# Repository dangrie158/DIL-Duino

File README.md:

# DIL-Duino

<br /><span xmlns:dct="http://purl.org/dc/terms/" property="dct:title">DIL-Duino</span> by <a xmlns:cc="http://creativecommons.org/ns#" href="http://www.nupo-artworks.de" property="cc:attributionName" rel="cc:attributionURL">Daniel Grießhaber</a> is licensed under a <a rel="license" href="http://creativecommons.org/licenses/by-sa/4.0/">Creative Commons Attribution-ShareAlike 4.0 International License</a>.<br />Based on a work at <a xmlns:dct="http://purl.org/dc/terms/" href="https://github.com/dangrie158/DIL-Duino" rel="dct:source">https://github.com/dangrie158/DIL-Duino</a>.

A complete Arduino environment in a DIL-8 form factor based on the DigiSpark Hardware

## Summary

DIL-Duino uses the QFN Version of the ATTiny85 and a USB Bootloader to provide the easy to use Arduino stack in a single DIL-8 Package Footprint. 
To fit the Micro-USB socket on the board, it was necessary to make the actual board bigger than the DIL Package, but after development the Board is perforated to break the USB Socket and get the desired footprint. 

The pinout matches the ATTiny85 so it can be used as a drop-in replacement

## Links

This Project on (Hackaday)[https://hackaday.io/project/8301-dil-duino]

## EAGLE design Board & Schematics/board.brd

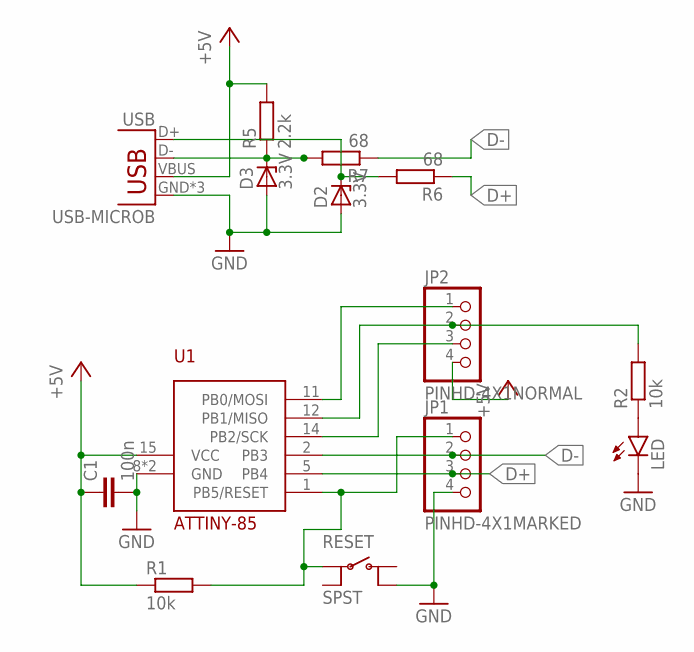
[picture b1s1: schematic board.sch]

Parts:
C1: 100n; C0603
D2, D3: 3.3V; SOD80C
JP1: PINHD-4X1MARKED; PINHD-1X4-MARKED
JP2: PINHD-4X1NORMAL; PINHD-1X4
LED: LED0603; LED-0603
R1, R2: 10k; R0402
R5: 2.2k; R0402
R6, R7: 68; R0402
RESET: SPST; WUERTH-SPST-SMD
U1: ATTINY-85; QFN20
USB: USB-MICROB

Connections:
+5V: C1.1, JP2.4, R1.1, R5.2, U1.15 (VCC), USB.VBUS
D+: JP1.3, R6.1, U1.5 (PB4)
D-: JP1.2, R7.1, U1.2 (PB3)
GND: C1.2, D2.A, D3.A, JP1.4, LED.C, RESET.4 (O2), U1.8 (GND), U1.EP (GND), USB.GND, USB.MT1 (GND), USB.MT2 (GND)
unnamed: JP1.1, R1.2, RESET.1, U1.1 (PB5/RESET)
unnamed: JP2.1, U1.11 (PB0/MOSI)
unnamed: LED.A, R2.1
unnamed: D3.C, R5.1, R7.2, USB.D-
unnamed: D2.C, R6.2, USB.D+
unnamed: JP2.3, U1.14 (PB2/SCK)
unnamed: JP2.2, R2.2, U1.12 (PB1/MISO)

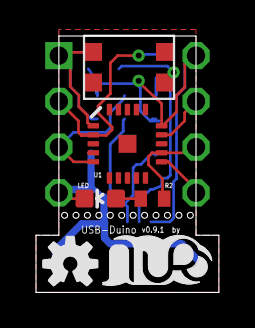
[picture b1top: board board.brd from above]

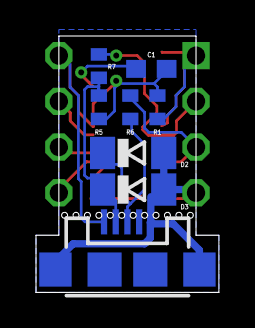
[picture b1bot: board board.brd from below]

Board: 2 copper layers, 10.2 x 14.2 mm, 16 parts (8 on the bottom side), 11 nets.

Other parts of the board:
U$1: OSHW-LOGO-S
U$2: LOGO-SILKSCREEEN-S

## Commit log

2015-11-07 added README with Project information
2015-11-07 added Licence Information to README
2015-11-07 added first version of the board and schematic
2015-11-07 added reset switch to support bootloader
2015-11-07 added share-alike clause
2015-12-02 added gerbers

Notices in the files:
parts and their libraries:
SparkFun-LED: Licensing: Creative Commons ShareAlike 4.0 International - https://creativecommons.org/licenses/by-sa/4.0
